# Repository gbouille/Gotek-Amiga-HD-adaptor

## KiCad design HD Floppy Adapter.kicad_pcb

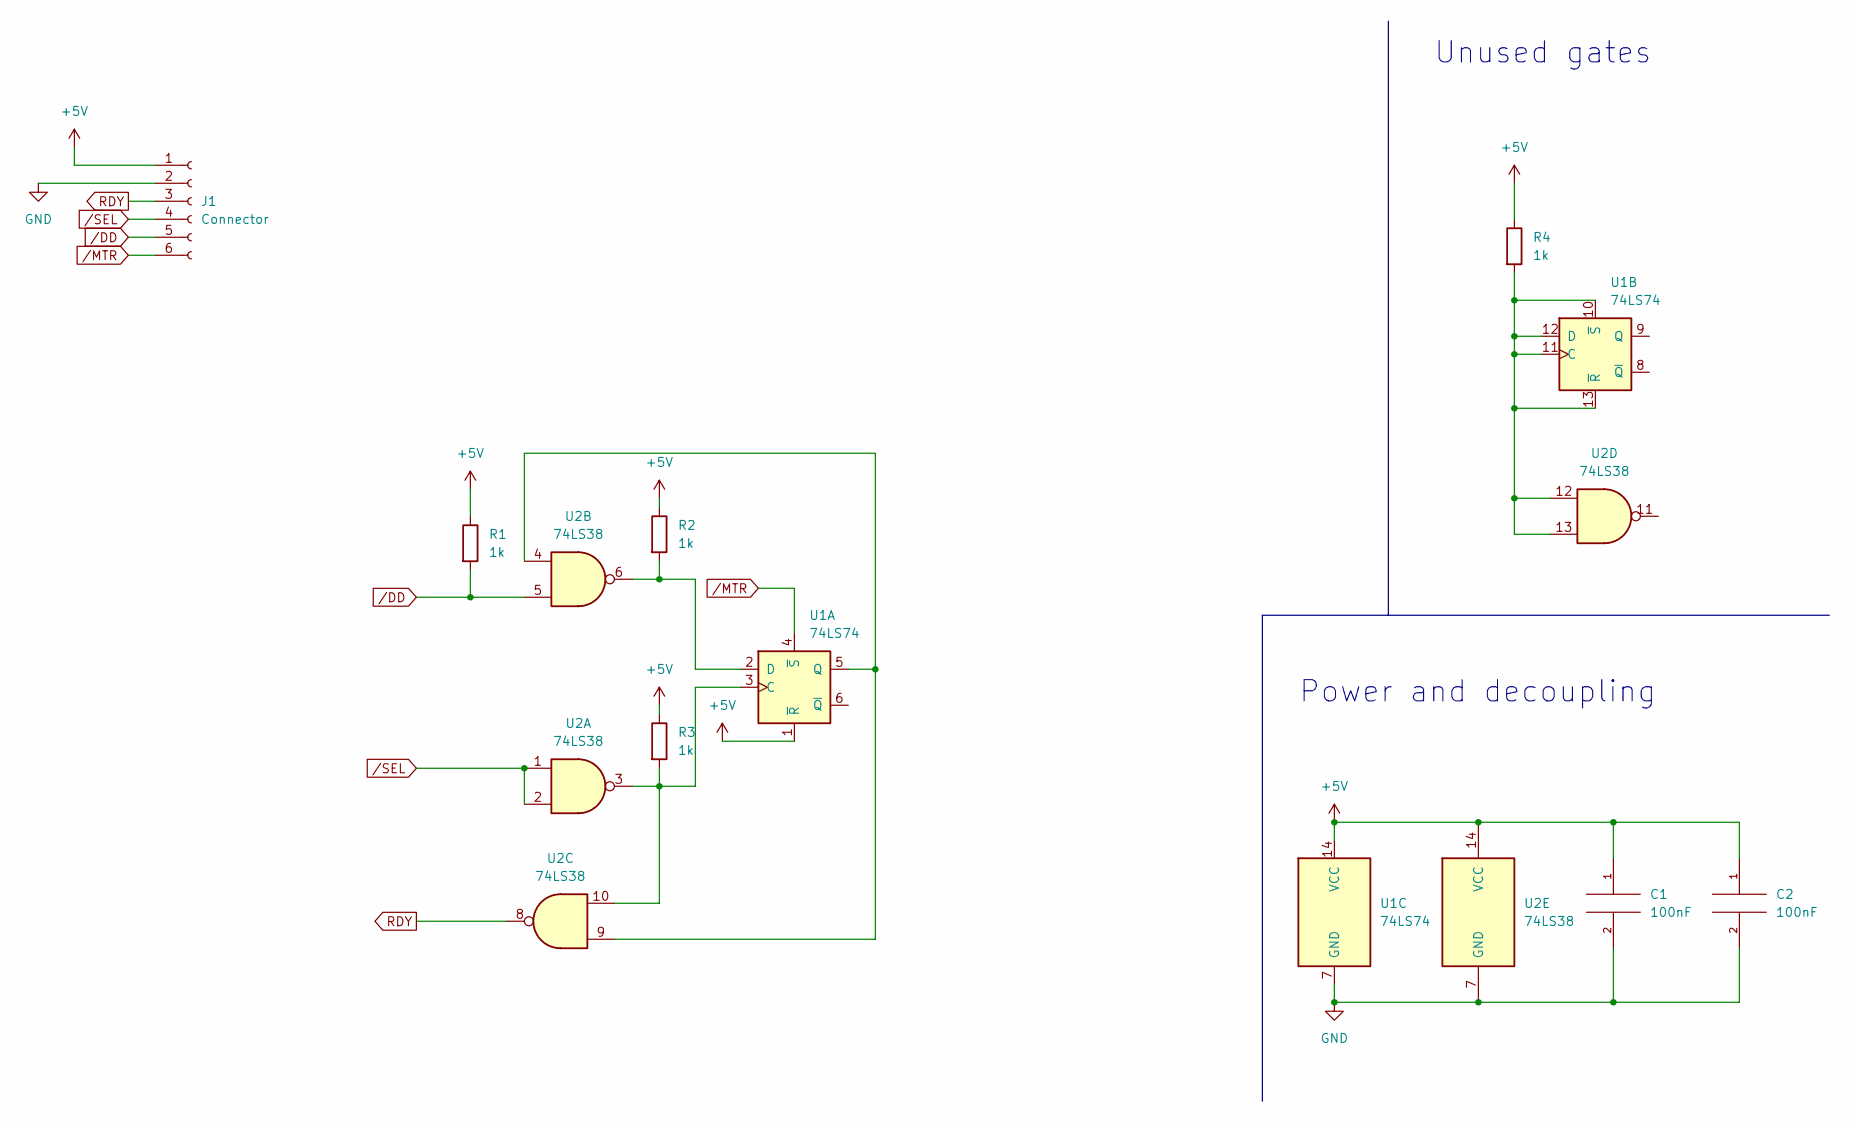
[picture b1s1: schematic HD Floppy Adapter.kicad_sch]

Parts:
C1, C2: 100nF; C_0805_2012Metric
J1: Connector; PinHeader_1x06_P2.54mm_Vertical
R1, R2, R3, R4: 1k; R_0805_2012Metric_Pad1.20x1.40mm_HandSolder
U1: 74LS74; SOIC-14_3.9x8.7mm_P1.27mm
U2: 74LS38; SOIC-14_3.9x8.7mm_P1.27mm

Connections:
+5V: C1.1, C2.1, J1.1, R1.1, R2.1, R3.1, R4.1, U1.1 (~R), U1.14 (VCC), U2.14 (VCC)
GND: C1.2, C2.2, J1.2, U1.7 (GND), U2.7 (GND)
unnamed: R2.2, U1.2 (D), U2.6
unnamed: R3.2, U1.3 (C), U2.3, U2.10
unnamed: R4.2, U1.10 (~S), U1.11 (C), U1.12 (D), U1.13 (~R), U2.12, U2.13
unnamed: U1.5 (Q), U2.4, U2.9
RDY: J1.3, U2.8
/DD: J1.5, R1.2, U2.5
/MTR: J1.6, U1.4 (~S)
/SEL: J1.4, U2.1, U2.2

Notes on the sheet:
Power and decoupling
Unused gates

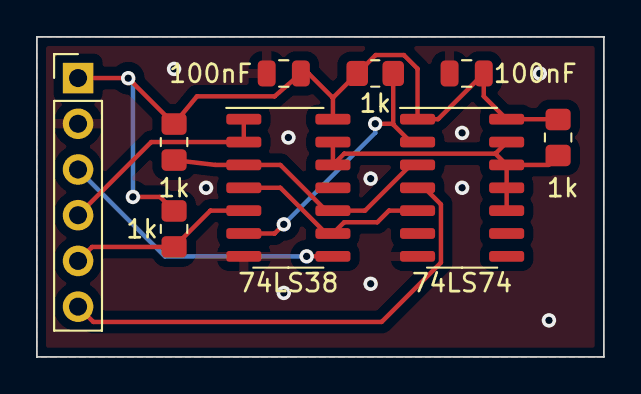
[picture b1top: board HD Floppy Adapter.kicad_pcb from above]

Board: 2 copper layers, 31.5 x 17.8 mm, 9 parts (0 on the bottom side), 10 nets.

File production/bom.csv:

Designator,Footprint,Quantity,Value,LCSC Part #
"C1, C2",C_0805_2012Metric,2,100nF,
J1,PinHeader_1x06_P2.54mm_Vertical,1,Conn_01x06_Female,
"R1, R2",R_0805_2012Metric_Pad1.20x1.40mm_HandSolder,2,1k,
R3,R_0805_2012Metric_Pad1.20x1.40mm_HandSolder,1,150,
R4,R_0805_2012Metric_Pad1.20x1.40mm_HandSolder,1,470,
U1,SOIC-14_3.9x8.7mm_P1.27mm,1,74LS74,
U2,SOIC-14_3.9x8.7mm_P1.27mm,1,74LS38,

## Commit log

2022-10-02 First version
    First version of the board
